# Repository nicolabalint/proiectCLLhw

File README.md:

# Proiect PCB – Sistem embedded cu microcontroler, LCD și senzori

## Descriere
Acest repository conține proiectarea completă a unui **sistem embedded pe placă de circuit imprimat (PCB)**, realizat în KiCad. Proiectul integrează un **microcontroler**, un **afișaj LCD**, circuite de **semnalizare LED**, **buzzer**, monitorizare baterie și **senzor de temperatură**, precum și partea de **alimentare și reglare tensiune**.

Proiectul include:
- schematic electric modular
- layout PCB (rutare pe mai multe straturi)
- conectori, componente discrete și circuite auxiliare
- găuri de montaj și delimitări mecanice

---

## Schematic

---

## Layout PCB

---

## Tehnologii și unelte utilizate

- **KiCad** (schematic + PCB layout)
- Proiectare PCB
- Circuite digitale și analogice
- Alimentare stabilizată la 5V
- Microcontroler + periferice

---

## Structura funcțională a proiectului

```text
│   cll.kicad_pcb
│   cll.kicad_prl
│   cll.kicad_pro
│   cll.kicad_sch
│   cll.net
│   fp-info-cache

```
## Descrierea blocurilor funcționale

### REGULATOR 100

Blocul de alimentare asigură:

- protecția la polaritate inversă
- stabilizarea tensiunii de alimentare la **5V**
- filtrarea zgomotului prin condensatori de decuplare

Acest bloc furnizează tensiunea necesară tuturor modulelor din sistem.

---

### uC 200 – Microcontroler

Microcontrolerul reprezintă unitatea centrală de comandă și control:

- gestionează comunicația cu LCD-ul
- controlează LED-urile și buzzer-ul
- citește informații de la senzorul de temperatură
- monitorizează nivelul bateriei

Include:

- conector de programare/debug
- rezistențe și condensatori de decuplare
- pini dedicați pentru periferice

---

### LCD 300

Blocul LCD permite afișarea informațiilor către utilizator:

- date de stare
- mesaje informative
- valori măsurate

Conectarea este realizată printr-o interfață paralelă, cu rezistențe de limitare și control pentru iluminarea de fundal.

---

### LED 400

Circuitul de LED-uri este utilizat pentru semnalizare vizuală:

- stări de funcționare
- avertizări

Fiecare LED este comandat prin tranzistor și rezistențe de polarizare, asigurând protecția microcontrolerului.

---

### BUZZER 500

Blocul de buzzer oferă semnalizare acustică:

- alarme
- notificări sonore

Comanda este realizată prin tranzistor, permițând acționarea buzzer-ului fără suprasolicitarea pinilor microcontrolerului.

---

### MON_BAT 600 – Monitorizare baterie

Acest bloc permite:

- monitorizarea tensiunii bateriei
- generarea de semnale de avertizare pentru nivel scăzut

Circuitul este realizat cu tranzistoare și divizoare rezistive pentru adaptarea nivelului de tensiune.

---

### TEMP 700 – Senzor de temperatură

Blocul de temperatură include:

- senzor dedicat
- filtrare cu condensatori
- conectare directă la microcontroler

Permite citirea temperaturii ambientale și afișarea acesteia pe LCD.

---

## Layout PCB

Layout-ul PCB:

- este realizat respectând regulile de proiectare
- include rutare clară a semnalelor digitale și analogice
- folosește plane de masă pentru reducerea zgomotului
- include găuri de montaj pentru fixarea plăcii

Componentele sunt grupate logic, conform blocurilor funcționale din schematic.

---

## Rezultate

- schematic modular și ușor de urmărit
- layout PCB coerent și echilibrat
- separare clară între alimentare, logică și sarcini
- sistem complet integrat pe o singură placă

---

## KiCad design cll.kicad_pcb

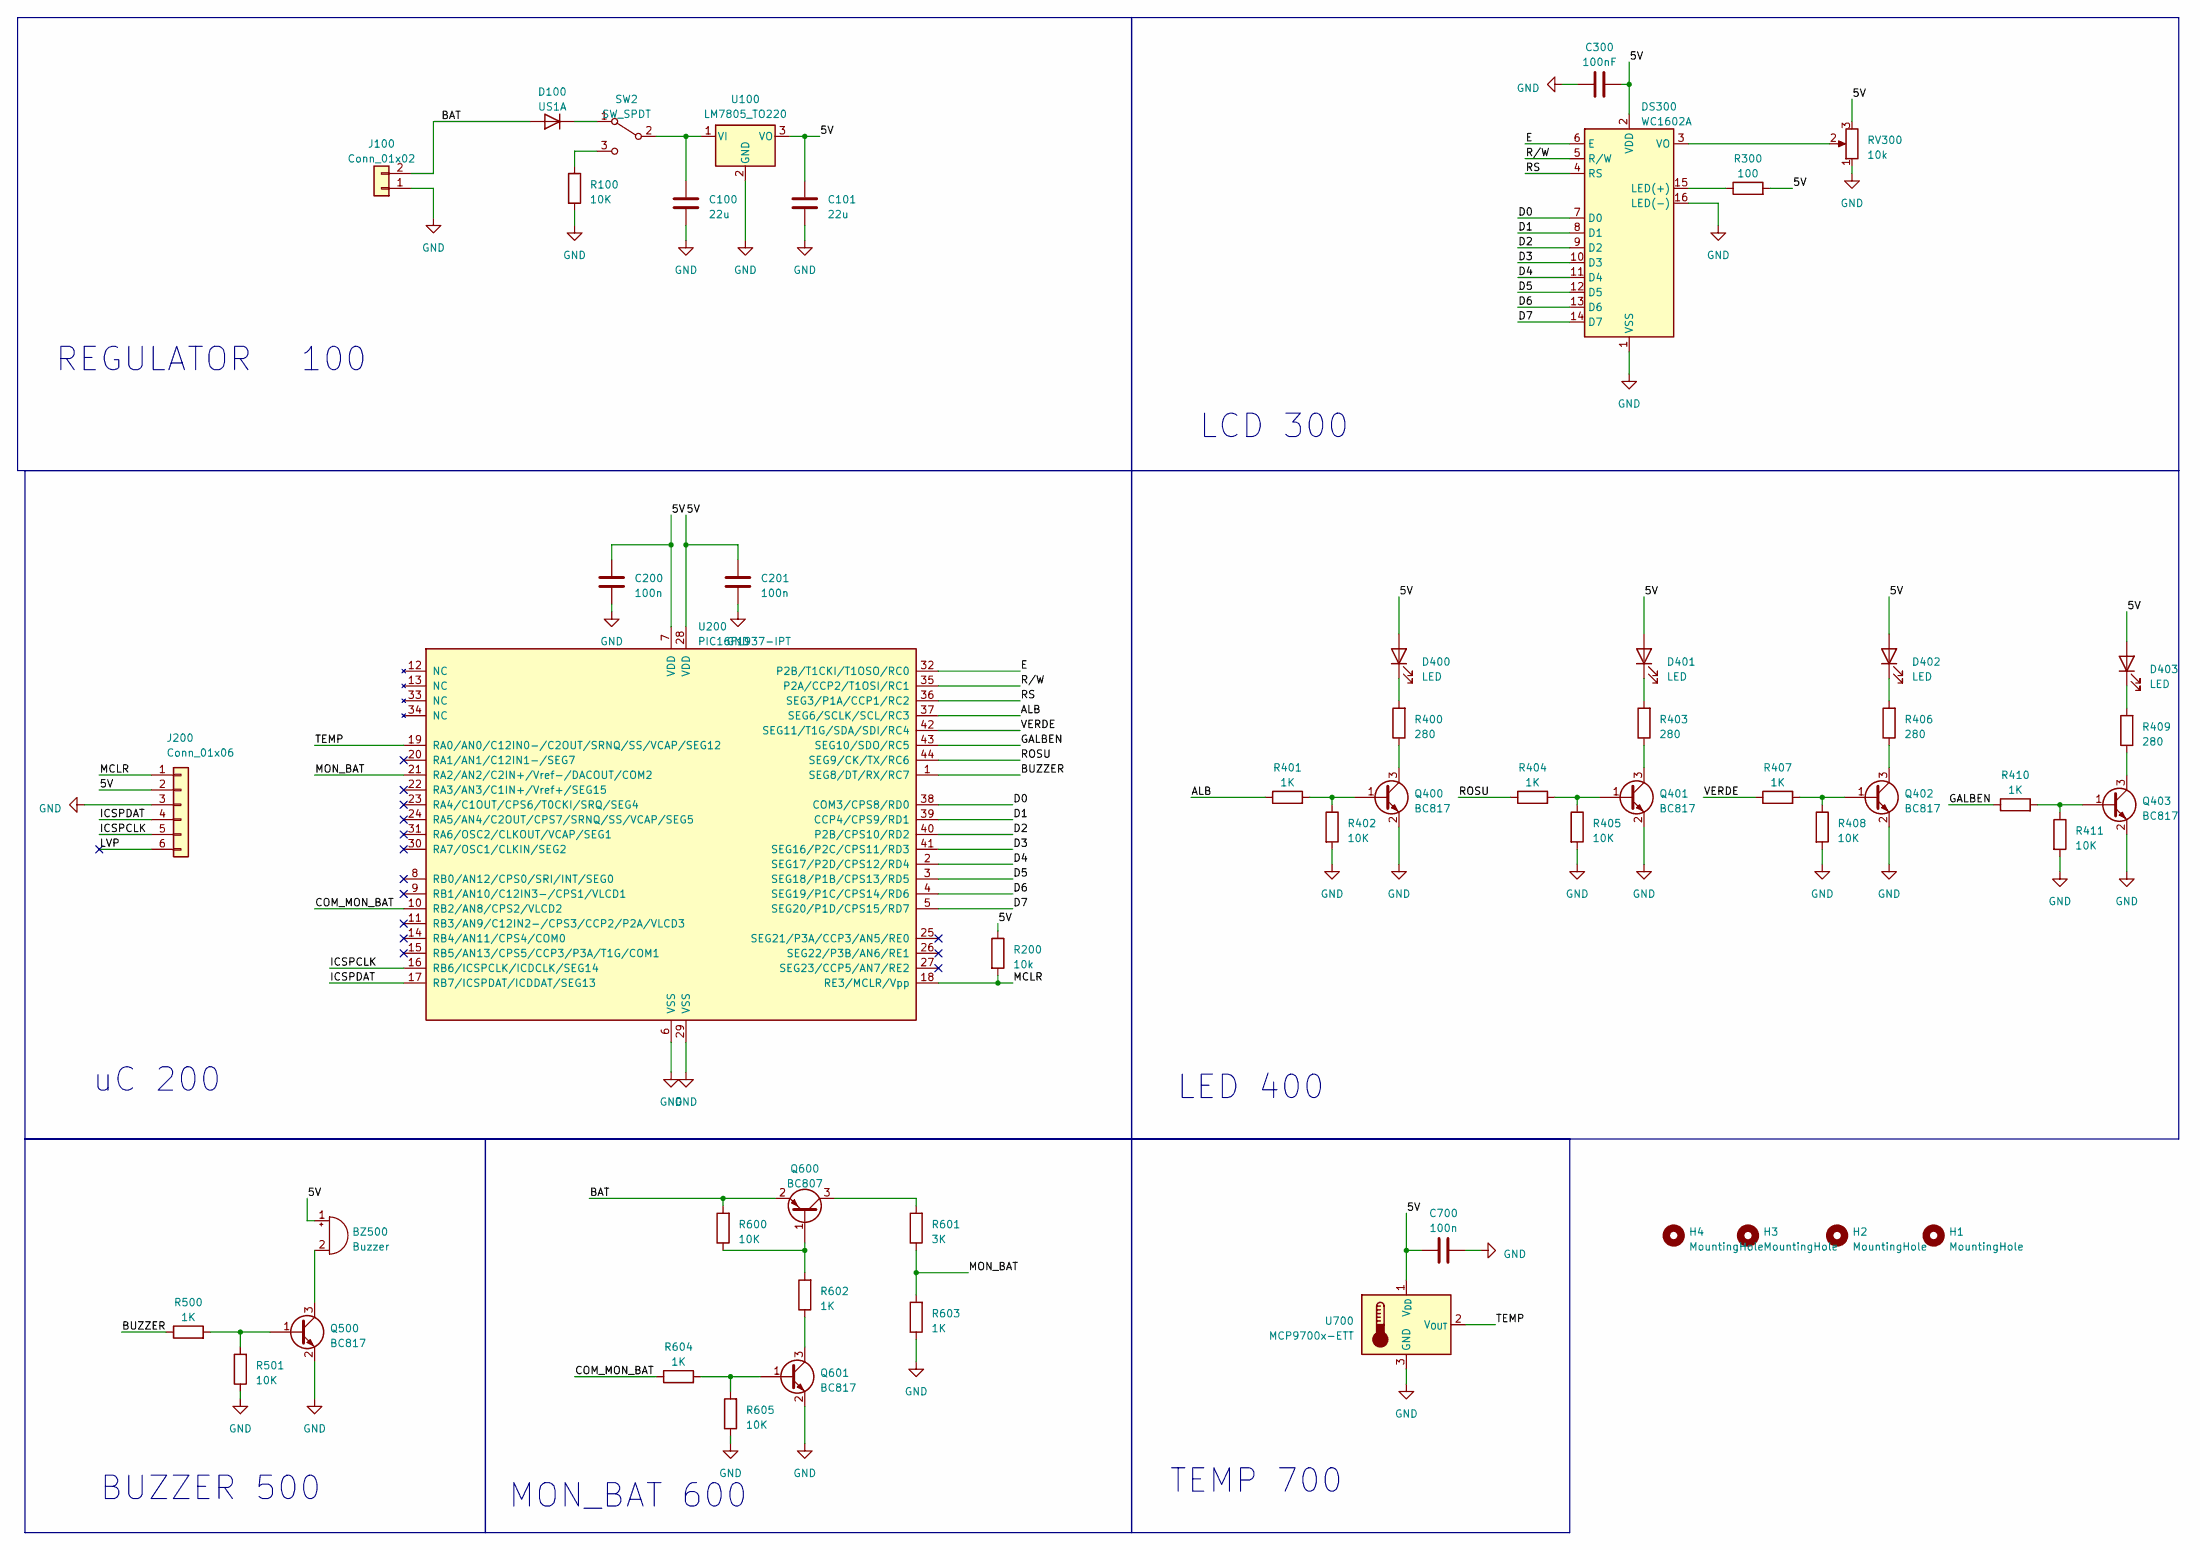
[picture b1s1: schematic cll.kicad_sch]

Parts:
BZ500: Buzzer; Buzzer_15x7.5RM7.6
C100, C101: 22u; C_1206_3216Metric_Pad1.33x1.80mm_HandSolder
C200, C201, C700: 100n; C_0805_2012Metric_Pad1.18x1.45mm_HandSolder
C300: 100nF; C_0805_2012Metric_Pad1.18x1.45mm_HandSolder
D100: US1A; D_SMA
D400, D401, D402, D403: LED; LED_0805_2012Metric_Pad1.15x1.40mm_HandSolder
DS300: WC1602A
H1, H2, H3, H4: MountingHole; MountingHole_4.3mm_M4_DIN965_Pad
J100: Conn_01x02; TerminalBlock_bornier-2_P5.08mm
J200: Conn_01x06; PinHeader_1x06_P2.54mm_Vertical
Q400, Q401, Q402, Q403, Q500, Q601: BC817; SOT-23
Q600: BC807; SOT-23
R100, R402, R405, R408, R411, R501, R600, R605: 10K; R_0805_2012Metric_Pad1.20x1.40mm_HandSolder
R200: 10k; R_0805_2012Metric_Pad1.20x1.40mm_HandSolder
R300: 100; R_0805_2012Metric_Pad1.20x1.40mm_HandSolder
R400, R403, R406, R409: 280; R_0805_2012Metric_Pad1.20x1.40mm_HandSolder
R401, R404, R407, R410, R500, R602, R603, R604: 1K; R_0805_2012Metric_Pad1.20x1.40mm_HandSolder
R601: 3K; R_0805_2012Metric_Pad1.20x1.40mm_HandSolder
RV300: 10k; Potentiometer_Bourns_3339H_Vertical
SW2: SW_SPDT; PinHeader_1x03_P2.54mm_Vertical
U100: LM7805_TO220; TO-220-3_Vertical
U200: PIC16F1937-IPT; TQFP-44_10x10mm_P0.8mm
U700: MCP9700x-ETT; SOT-23

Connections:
/5V: BZ500.1 (-), C101.1, C200.1, C201.1, C300.2, C700.1, D400.2 (A), D401.2 (A), D402.2 (A), D403.2 (A), DS300.2 (VDD), J200.2, R200.1, R300.2, RV300.3, U100.3 (VO), U200.7 (VDD), U200.28 (VDD), U700.1 (V_{DD})
/ALB: R401.1, U200.37 (SEG6/SCLK/SCL/RC3)
/BAT: D100.2 (A), J100.2, Q600.2 (E), R600.2
/BUZZER: R500.1, U200.1 (SEG8/DT/RX/RC7)
/COM_MON_BAT: R604.1, U200.10 (RB2/AN8/CPS2/VLCD2)
/D0: DS300.7 (D0), U200.38 (COM3/CPS8/RD0)
/D1: DS300.8 (D1), U200.39 (CCP4/CPS9/RD1)
/D2: DS300.9 (D2), U200.40 (P2B/CPS10/RD2)
/D3: DS300.10 (D3), U200.41 (SEG16/P2C/CPS11/RD3)
/D4: DS300.11 (D4), U200.2 (SEG17/P2D/CPS12/RD4)
/D5: DS300.12 (D5), U200.3 (SEG18/P1B/CPS13/RD5)
/D6: DS300.13 (D6), U200.4 (SEG19/P1C/CPS14/RD6)
/D7: DS300.14 (D7), U200.5 (SEG20/P1D/CPS15/RD7)
/E: DS300.6 (E), U200.32 (P2B/T1CKI/T1OSO/RC0)
/GALBEN: R410.1, U200.43 (SEG10/SDO/RC5)
/ICSPCLK: J200.5, U200.16 (RB6/ICSPCLK/ICDCLK/SEG14)
/ICSPDAT: J200.4, U200.17 (RB7/ICSPDAT/ICDDAT/SEG13)
/LVP: J200.6
/MCLR: J200.1, R200.2, U200.18 (RE3/MCLR/Vpp)
/MON_BAT: R601.1, R603.2, U200.21 (RA2/AN2/C2IN+/Vref-/DACOUT/COM2)
/ROSU: R404.1, U200.44 (SEG9/CK/TX/RC6)
/RS: DS300.4 (RS), U200.36 (SEG3/P1A/CCP1/RC2)
/R/W: DS300.5 (R/W), U200.35 (P2A/CCP2/T1OSI/RC1)
/TEMP: U200.19 (RA0/AN0/C12IN0-/C2OUT/SRNQ/SS/VCAP/SEG12), U700.2 (V_{OUT})
/VERDE: R407.1, U200.42 (SEG11/T1G/SDA/SDI/RC4)
GND: C100.2, C101.2, C200.2, C201.2, C300.1, C700.2, DS300.1 (VSS), DS300.16 (LED(-)), J100.1, J200.3, Q400.2 (E), Q401.2 (E), Q402.2 (E), Q403.2 (E), Q500.2 (E), Q601.2 (E), R100.2, R402.2, R405.2, R408.2, R411.2, R501.1, R603.1, R605.1, RV300.1, U100.2 (GND), U200.6 (VSS), U200.29 (VSS), U700.3 (GND)
unnamed: BZ500.2 (+), Q500.3 (C)
unnamed: D100.1 (K), SW2.1 (A)
unnamed: D400.1 (K), R400.2
unnamed: D401.1 (K), R403.2
unnamed: D402.1 (K), R406.2
unnamed: D403.1 (K), R409.2
unnamed: DS300.15 (LED(+)), R300.1
unnamed: DS300.3 (VO), RV300.2
unnamed: Q400.1 (B), R401.2, R402.1
unnamed: Q400.3 (C), R400.1
unnamed: Q401.1 (B), R404.2, R405.1
unnamed: Q401.3 (C), R403.1
unnamed: Q402.1 (B), R407.2, R408.1
unnamed: Q402.3 (C), R406.1
unnamed: Q403.1 (B), R410.2, R411.1
unnamed: Q403.3 (C), R409.1
unnamed: Q500.1 (B), R500.2, R501.2
unnamed: Q600.1 (B), R600.1, R602.2
unnamed: Q600.3 (C), R601.2
unnamed: Q601.1 (B), R604.2, R605.2
unnamed: Q601.3 (C), R602.1
unnamed: C100.1, SW2.2 (B), U100.1 (VI)
unnamed: R100.1, SW2.3 (C)

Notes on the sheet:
MON_BAT 600
LCD 300
uC 200
100
REGULATOR
TEMP 700
BUZZER 500
LED 400

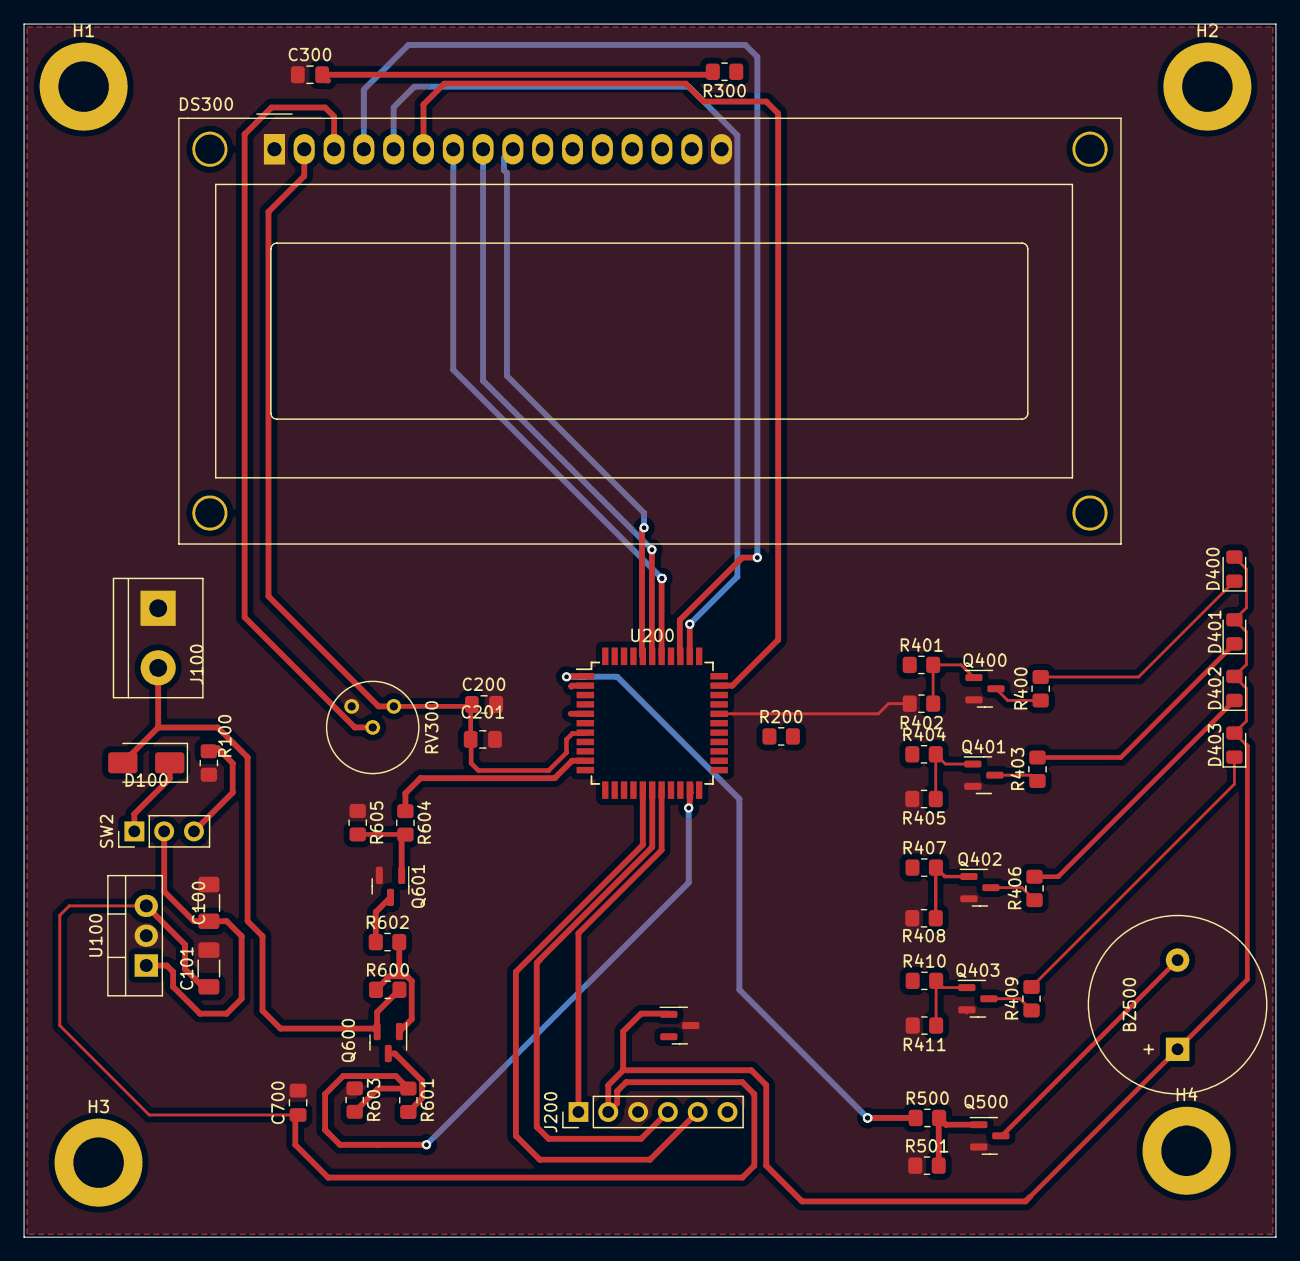
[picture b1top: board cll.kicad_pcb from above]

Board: 2 copper layers, 106.7 x 103.4 mm, 54 parts (0 on the bottom side), 48 nets.
